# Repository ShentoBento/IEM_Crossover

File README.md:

# IEM_Crossover
Crossover PCB Template for Multi-Driver IEMS

<p align="center">

<p align="center">

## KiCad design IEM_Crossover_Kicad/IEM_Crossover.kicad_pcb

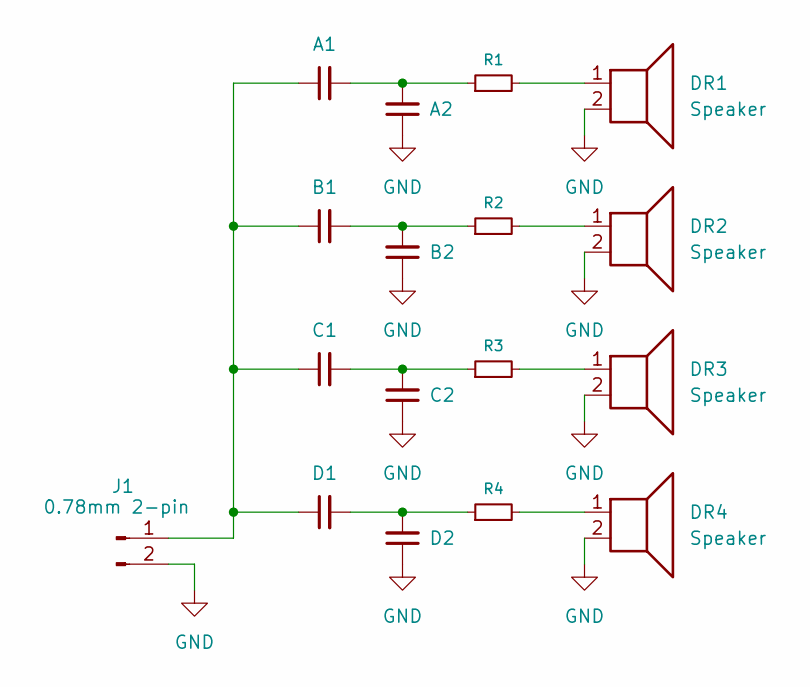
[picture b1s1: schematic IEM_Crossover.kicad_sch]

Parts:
A1, A2: C_Small; C_0805_2012Metric
B1, B2: C_Small; C_0805_2012Metric
C1, C2: C_Small; C_0805_2012Metric
D1, D2: C_Small; C_0805_2012Metric
DR1, DR2, DR3, DR4: Speaker; IEM_Driver_1x2_Pad
J1: 0.78mm 2-pin; IEM_Driver_1x2_Pad
R1, R2, R3, R4: R_Small; C_0805_2012Metric

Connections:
GND: A2.1, B2.1, C2.1, D2.1, DR1.2, DR2.2, DR3.2, DR4.2, J1.2
unnamed: A1.2, A2.2, R1.1
unnamed: B1.2, B2.2, R2.1
unnamed: C1.2, C2.2, R3.1
unnamed: D1.2, D2.2, R4.1
unnamed: DR1.1, R1.2
unnamed: DR2.1, R2.2
unnamed: DR3.1, R3.2
unnamed: DR4.1, R4.2
unnamed: A1.1, B1.1, C1.1, D1.1, J1.1

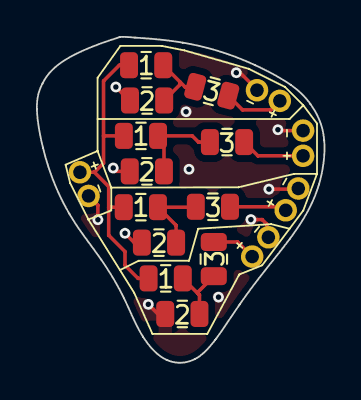
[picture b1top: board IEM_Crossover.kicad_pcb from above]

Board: 2 copper layers, 16.0 x 18.1 mm, 17 parts (0 on the bottom side), 10 nets.

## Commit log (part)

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2026-05-15 Added Kicad Files
2026-05-15 Added Branch 1, Created Driver Footprint
2026-05-15 Changed component footprints to 0805
